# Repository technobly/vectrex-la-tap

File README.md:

Vectrex LA TAP
===

The Vectrex LA Tap is a logic analyzer tap for the Vectrex. It also turns the cartridge to face the player.  Use it for technical debugging, or just as a way to display your running cartridge. Populate either the right-angle or straight male header for connections, or both.  I prefer the right-angle to keep the jumpers lower to the table where your logic analyzer is located.  This can also be used as a quick way to add RAM to a game if you don't have a multicart like [VEXTREME](https://github.com/technobly/VEXTREME) that can do that for you programmatically.

See it in action here:
https://www.youtube.com/watch?v=Tel6ZxioI6E

BOM and Parts ordering
===

- 1x - 36-pin Edge Connector [AMP 5645235-4](https://www.digikey.com/en/products/detail/te-connectivity-amp-connectors/5645235-4/1122061)

Optional Components
- 1x - 36-pin 2.54 mm dual-row right-angle male header [PH2RA-36-UA](https://www.digikey.com/en/products/detail/adam-tech/PH2RA-36-UA/9830520)
- 1x - 36-pin 2.54 mm dual-row straight male header [PRPC018DAAN-RC](https://www.digikey.com/en/products/detail/sullins-connector-solutions/PRPC018DAAN-RC/2775276)
- 1x - [0.1uF 0805 capacitor](https://www.digikey.com/en/products/detail/avx-corporation/08055C104KAT2A/563505)

Ordering PCB's
===

OSHPark is a good place to order with purple or the new "after dark" theme color scheme.  You can upload the KiCad `vextrex-la-tap.kicad_pcb` there directly.  I would download this entire Github repo ZIP file first though instead of just trying to save the PCB file from your browser.

Another way to order PCB's is by using the included [gerbers](gerbers/vectrex-la-tap-v1.0.zip) and uploading those with all of the necessary specs to companies like [PCBWay](https://www.pcbway.com) or [JLCPCB](https://jlcpcb.com)

If you want to make it fancy, don't forget to make your board finish ENIG (gold flash) with a 45 degree chamfered edge.  I ended up making these really cheap with HASL finish since I won't be using them that frequently.

LICENSE
===

Creative Commons Attribution-ShareAlike 4.0 International (CC BY-SA 4.0) - essentially do whatever you want, and if this is helpful to you [consider buying me a coffee](https://buymeacoffee.com/walach)  Full [LICENSE here](LICENSE)

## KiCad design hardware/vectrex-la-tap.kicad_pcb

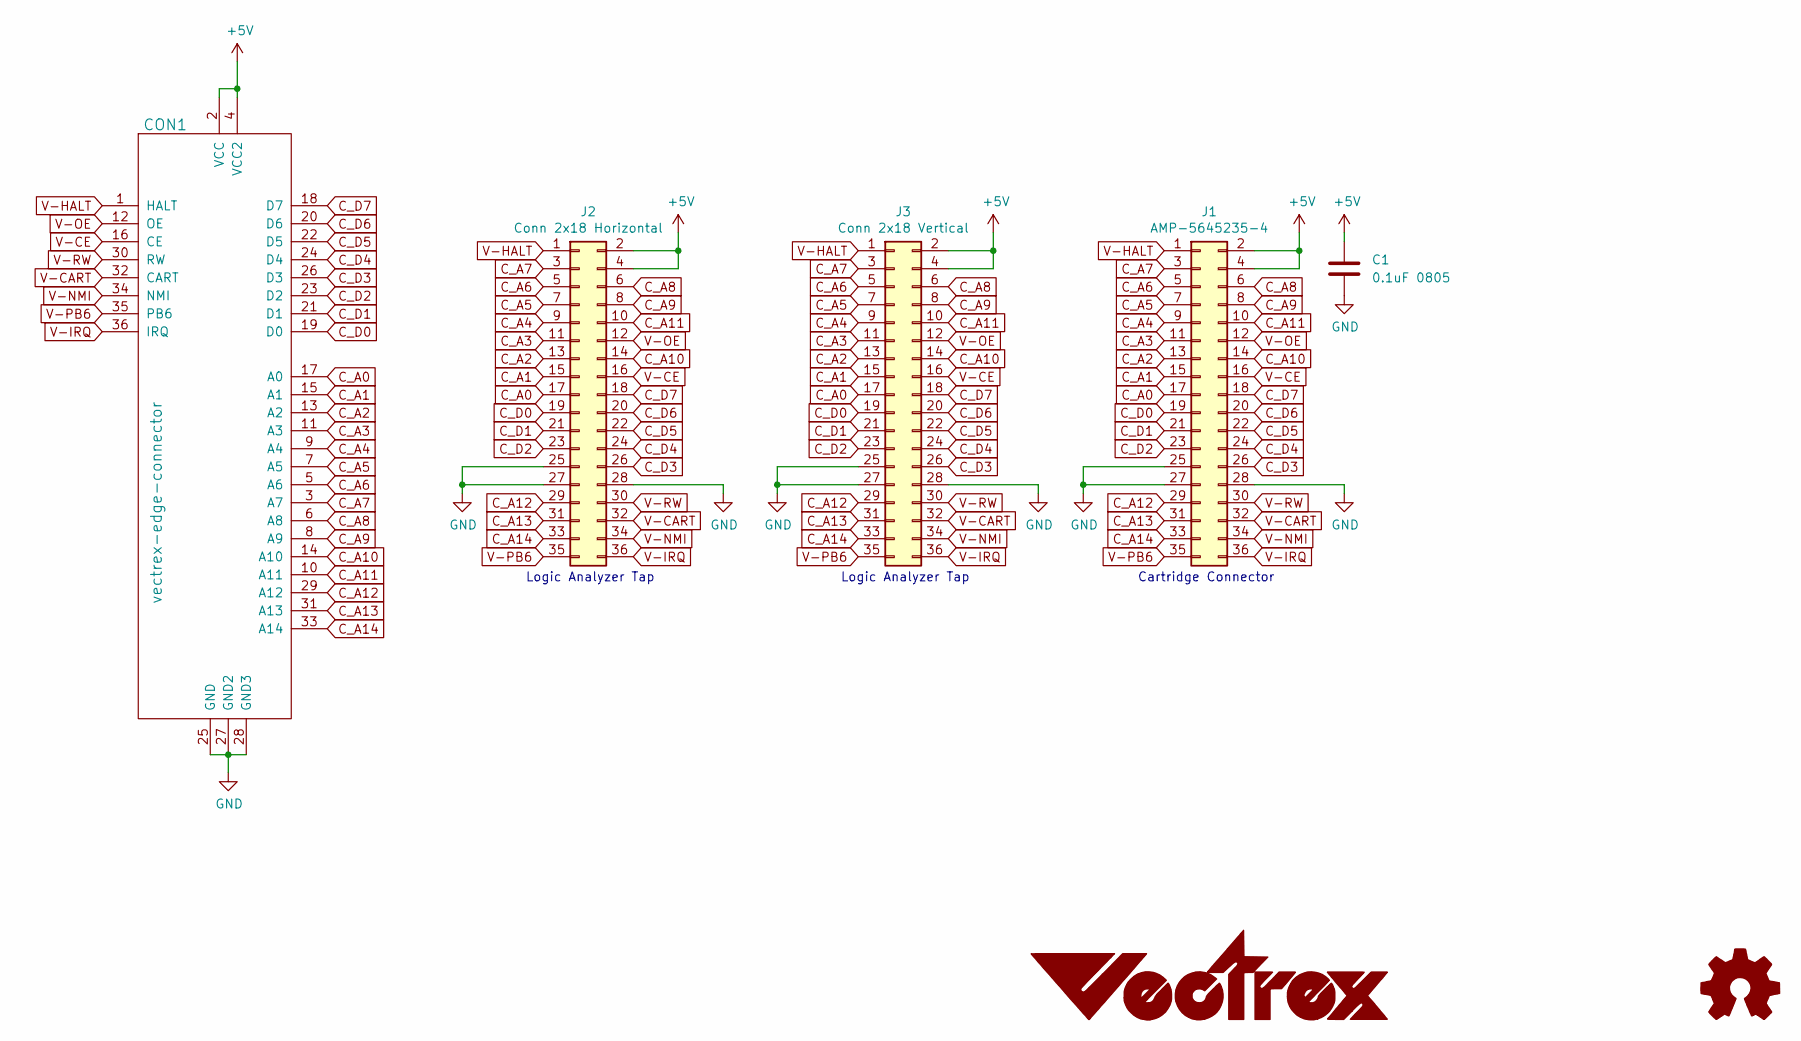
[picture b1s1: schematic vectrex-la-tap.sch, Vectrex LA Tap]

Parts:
C1: 0.1uF 0805; C_0805_2012Metric_Pad1.15x1.40mm_HandSolder
CON1: vectrex-edge-connector; vectrex-edge-connector-thinner-no-soldermask
G1: LOGO; vectrex-us-silkscreen
J1: AMP-5645235-4; AMP_5645235-4_2x18_P2.54mm_Vertical
J2: Conn 2x18 Horizontal; PinHeader_2x18_P2.54mm_Horizontal
J3: Conn 2x18 Vertical; PinHeader_2x18_P2.54mm_Vertical

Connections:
+5V: C1.1, CON1.2 (VCC), CON1.4 (VCC2), J1.2, J1.4, J2.2, J2.4, J3.2, J3.4
C_A0: CON1.17 (A0), J1.17, J2.17, J3.17
C_A1: CON1.15 (A1), J1.15, J2.15, J3.15
C_A2: CON1.13 (A2), J1.13, J2.13, J3.13
C_A3: CON1.11 (A3), J1.11, J2.11, J3.11
C_A4: CON1.9 (A4), J1.9, J2.9, J3.9
C_A5: CON1.7 (A5), J1.7, J2.7, J3.7
C_A6: CON1.5 (A6), J1.5, J2.5, J3.5
C_A7: CON1.3 (A7), J1.3, J2.3, J3.3
C_A8: CON1.6 (A8), J1.6, J2.6, J3.6
C_A9: CON1.8 (A9), J1.8, J2.8, J3.8
C_A10: CON1.14 (A10), J1.14, J2.14, J3.14
C_A11: CON1.10 (A11), J1.10, J2.10, J3.10
C_A12: CON1.29 (A12), J1.29, J2.29, J3.29
C_A13: CON1.31 (A13), J1.31, J2.31, J3.31
C_A14: CON1.33 (A14), J1.33, J2.33, J3.33
C_D0: CON1.19 (D0), J1.19, J2.19, J3.19
C_D1: CON1.21 (D1), J1.21, J2.21, J3.21
C_D2: CON1.23 (D2), J1.23, J2.23, J3.23
C_D3: CON1.26 (D3), J1.26, J2.26, J3.26
C_D4: CON1.24 (D4), J1.24, J2.24, J3.24
C_D5: CON1.22 (D5), J1.22, J2.22, J3.22
C_D6: CON1.20 (D6), J1.20, J2.20, J3.20
C_D7: CON1.18 (D7), J1.18, J2.18, J3.18
GND: C1.2, CON1.25 (GND), CON1.27 (GND2), CON1.28 (GND3), J1.25, J1.27, J1.28, J2.25, J2.27, J2.28, J3.25, J3.27, J3.28
V-CART: CON1.32 (CART), J1.32, J2.32, J3.32
V-CE: CON1.16 (CE), J1.16, J2.16, J3.16
V-HALT: CON1.1 (HALT), J1.1, J2.1, J3.1
V-IRQ: CON1.36 (IRQ), J1.36, J2.36, J3.36
V-NMI: CON1.34 (NMI), J1.34, J2.34, J3.34
V-OE: CON1.12 (OE), J1.12, J2.12, J3.12
V-PB6: CON1.35 (PB6), J1.35, J2.35, J3.35
V-RW: CON1.30 (RW), J1.30, J2.30, J3.30

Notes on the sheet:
Cartridge Connector
Logic Analyzer Tap

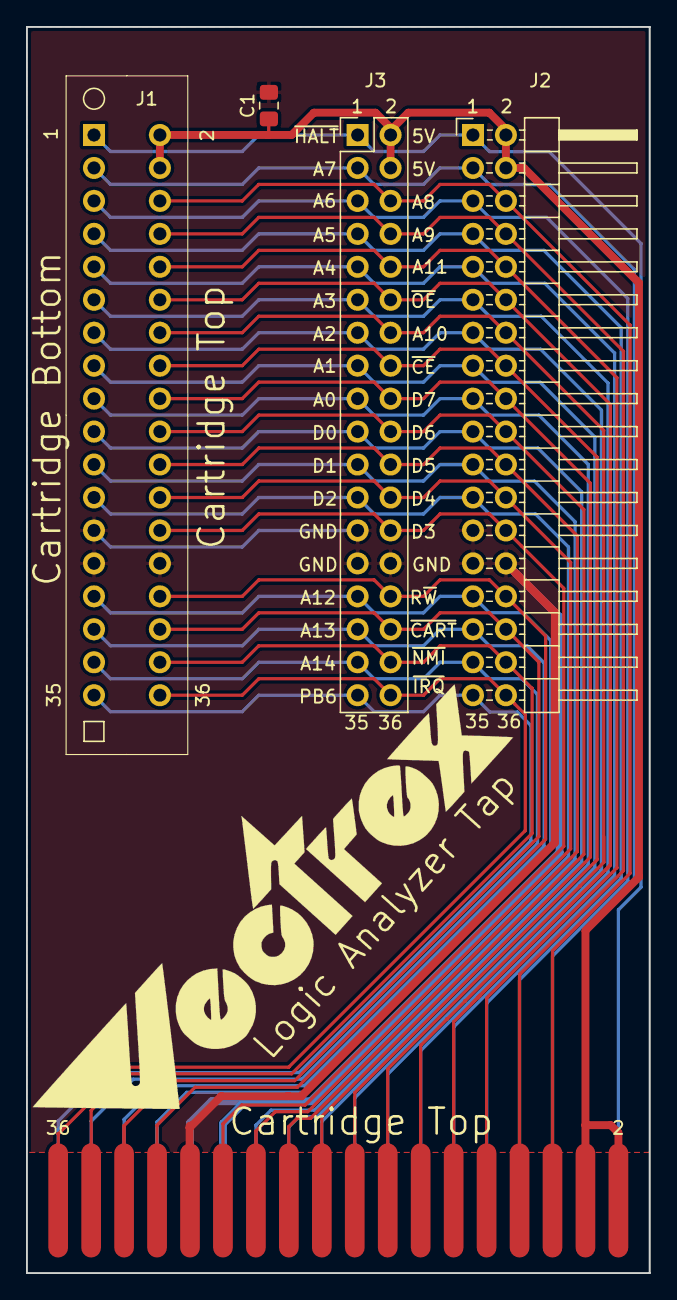
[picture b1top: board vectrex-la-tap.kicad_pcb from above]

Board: 2 copper layers, 48.0 x 96.1 mm, 6 parts (0 on the bottom side), 33 nets.

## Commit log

2021-08-21 initial release v1.1
